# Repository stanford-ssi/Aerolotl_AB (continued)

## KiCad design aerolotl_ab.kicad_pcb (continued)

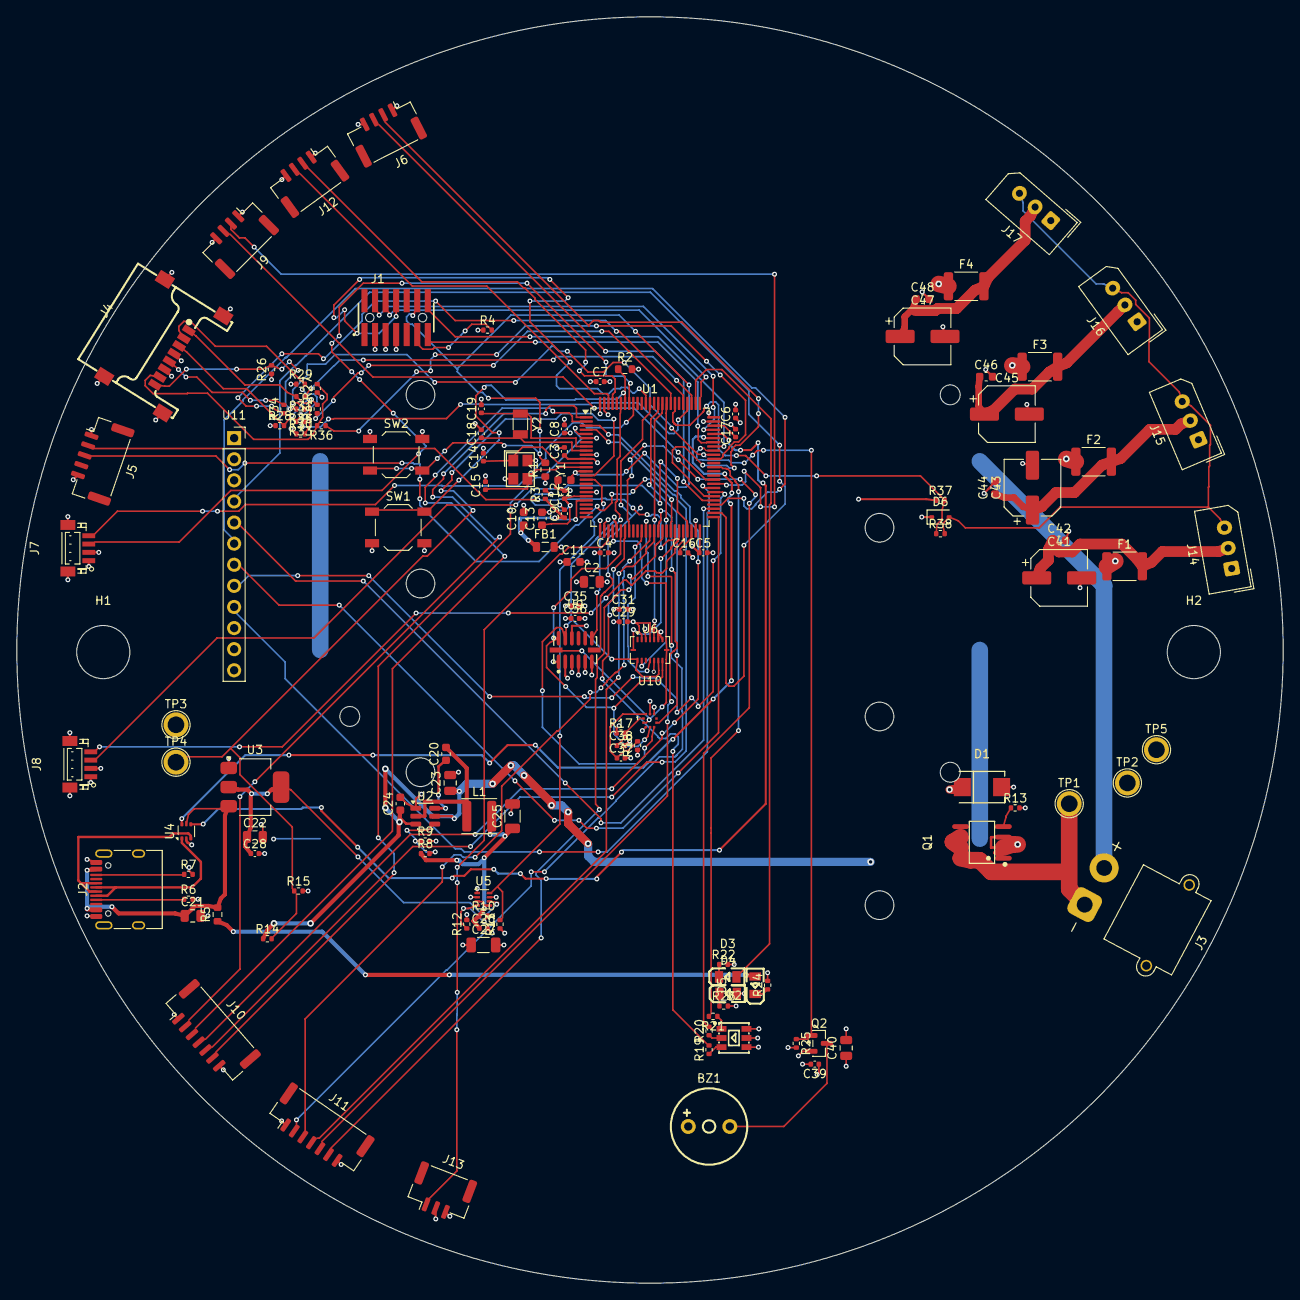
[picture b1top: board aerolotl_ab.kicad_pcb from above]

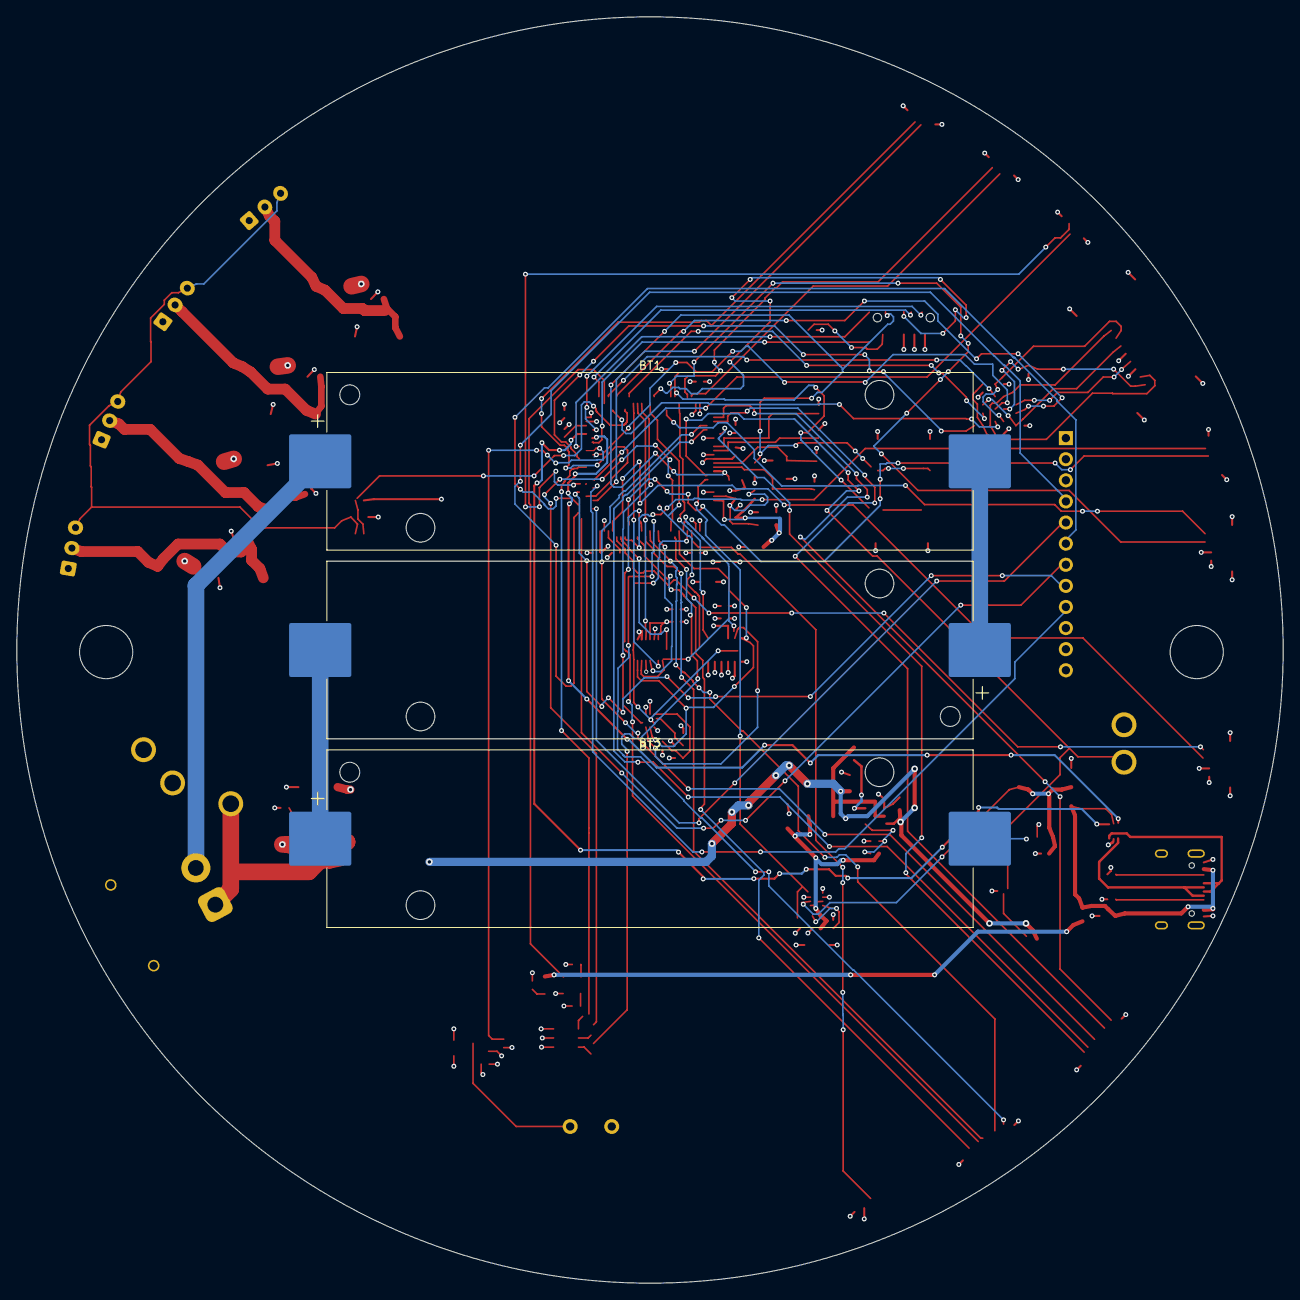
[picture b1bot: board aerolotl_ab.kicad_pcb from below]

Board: 4 copper layers, 152.4 x 152.4 mm, 136 parts (3 on the bottom side), 113 nets.
